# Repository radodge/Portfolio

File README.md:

# Engineering Project Portfolio

Welcome to my collection of hardware and software projects developed through coursework and personal experimentation. This repository gathers small demos and complete applications spanning digital logic design, embedded C programming, PCB layout, ASIC development, and Python-based computer vision image processing.

## Project Index
> Use the categories below to jump directly to work that matches the relevant skills you're interested in.
### Computer Vision Image Processing & Automation
- [Photo Digitization Application - v0](https://github.com/radodge/photo-digitization-v0) – Legacy implementation of my photo 'digitization' Python application.

### Embedded Systems Design
- [CPRE 288 Final Project](CPRE%20288%20Final%20Project/) – Embedded C code for robot movement, sensor processing, and driver abstractions.

### Digital VLSI
- [32-bit CPU Components](32-bit%20CPU%20Components/) – VHDL building blocks for a 32-bit MIPS CPU.
- [Moving Average and Std Dev ASIC](Moving%20Average%20and%20Std%20Dev%20ASIC/) – Custom Verilog ASIC implementing real time computation of moving average and standard deviation.

### PCB Design
- [KiCad Projects](KiCad%20Projects/) – Schematics and board layouts such as an adjustable power supply and a reprogrammable Game Boy Advance cartridge.

## Contact
Questions or collaboration inquiries? Reach out via email at dodger1846@icloud.com or connect on [LinkedIn](https://www.linkedin.com/in/reece-dodge).

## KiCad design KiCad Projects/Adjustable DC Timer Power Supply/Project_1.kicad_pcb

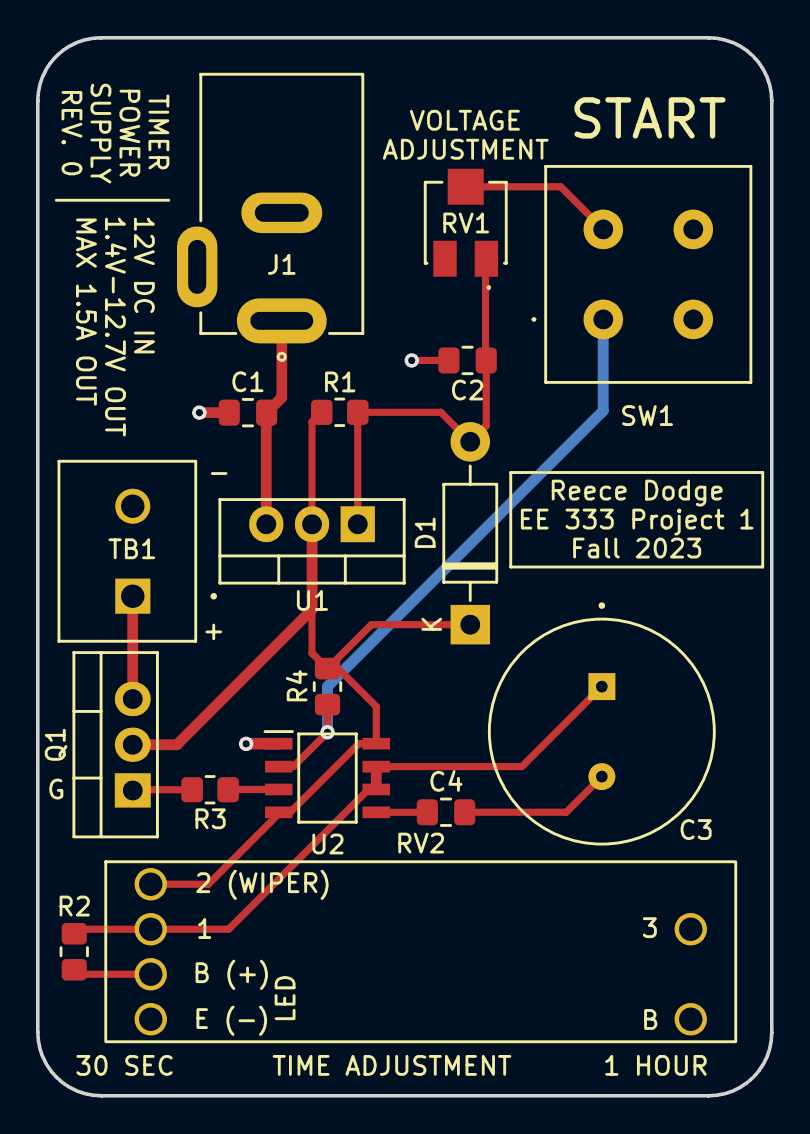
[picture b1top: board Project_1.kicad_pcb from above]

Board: 2 copper layers, 40.8 x 58.8 mm, 17 parts (0 on the bottom side), 11 nets.

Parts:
C1, C2: 10uF; C_0805_2012Metric_Pad1.18x1.45mm_HandSolder
C3: 3300uF; ECA-1CHG332
C4: 0.1uF; C_0805_2012Metric_Pad1.18x1.45mm_HandSolder
D1: 1N4002; D_DO-41_SOD81_P10.16mm_Horizontal
J1: PJ-002A
Q1: Q_NMOS_GDS; TO-220-3_Vertical
R1: 240; R_0805_2012Metric_Pad1.20x1.40mm_HandSolder
R2, R3, R4: 10K; R_0805_2012Metric_Pad1.20x1.40mm_HandSolder
RV1: 2.2K; TRIM_3314J-1-222E
RV2: PTL20-10O0-105B2
SW1: START; D6C90F2LFS
TB1: TB002-500-02BE; CUI_TB002-500-02BE
U1: LM317_SOT-223; TO-220-3_Vertical
U2: NE555D; SOIC127P600X175-8N

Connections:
/V_out: D1.1 (K), Q1.2 (D), R1.1, R4.2, RV2.2 (WIPER), U1.2 (VO), U2.4 (R), U2.8 (VCC)
GND: C1.1, C2.2, C3.N, C4.2, J1.2, RV1.2, RV2.E, SW1.3 (NO_1), TB1.2, U2.1 (GND)
unnamed: C2.1, D1.2 (A), R1.2, RV1.1, U1.1 (ADJ)
unnamed: Q1.1 (G), R3.2
unnamed: Q1.3 (S), TB1.1
unnamed: R2.2, RV2.L
unnamed: C3.P, R2.1, RV2.1 (CCW), U2.6 (THR), U2.7 (DIS)
unnamed: R4.1, SW1.1 (COM_1), U2.2 (TR)
unnamed: C1.2, J1.1, U1.3 (VI)
unnamed: C4.1, U2.5 (CV)
unnamed: R3.1, U2.3 (Q)

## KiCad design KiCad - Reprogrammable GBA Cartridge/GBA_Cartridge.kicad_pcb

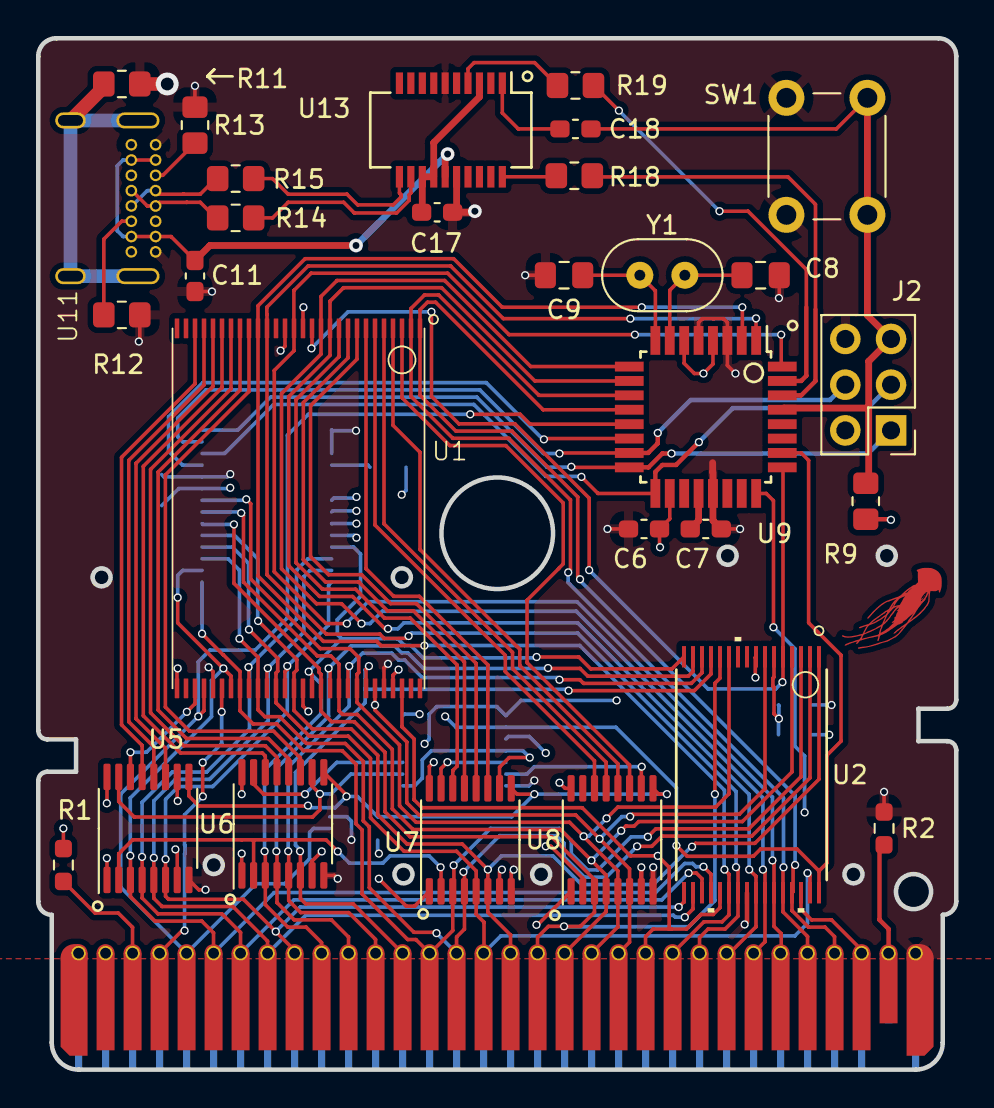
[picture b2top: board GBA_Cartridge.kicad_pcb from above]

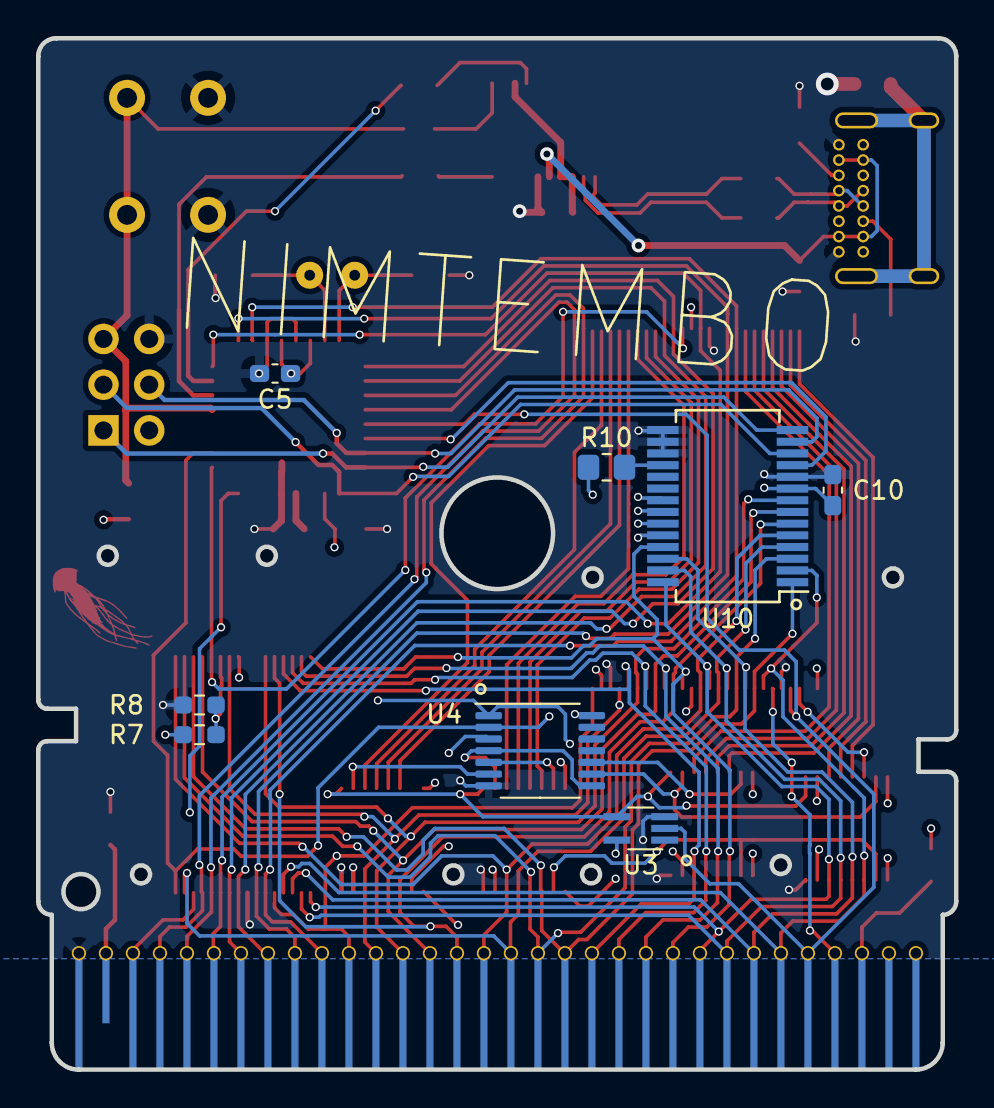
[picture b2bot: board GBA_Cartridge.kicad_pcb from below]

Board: 4 copper layers, 51.0 x 57.3 mm, 39 parts (8 on the bottom side), 78 nets.

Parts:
C5, C6, C7, C10, C17, C18: 0.1uF; C_0603_1608Metric_Pad1.08x0.95mm_HandSolder
C8, C9: 22pF; C_0805_2012Metric_Pad1.18x1.45mm_HandSolder
C11: 10nF; C_0603_1608Metric_Pad1.08x0.95mm_HandSolder
COS1: important
J1: Conn_01x32; GAYBUS
J2: Conn_02x03_Odd_Even; PinHeader_2x03_P2.54mm_Vertical
R1, R2, R7, R8: DNU; R_0603_1608Metric_Pad0.98x0.95mm_HandSolder
R9, R18, R19: 1k; R_0805_2012Metric_Pad1.20x1.40mm_HandSolder
R10: 10k; R_0805_2012Metric_Pad1.20x1.40mm_HandSolder
R11: 1M; R_0805_2012Metric_Pad1.20x1.40mm_HandSolder
R12, R13: 5.11k; R_0805_2012Metric_Pad1.20x1.40mm_HandSolder
R14, R15: 27R; R_0805_2012Metric_Pad1.20x1.40mm_HandSolder
SW1: SW_Push; SW_PUSH_6mm
U1: MT28EW256ABA1LJS-0SIT; 56-TFSOP (18.40mm Width)
U2: FM28V100-TG; TSOP-32
U3: 74AHC1G14SE-7; SOT-353_SC-70-5_Handsoldering
U4: 74LS08; TSSOP-14_4.4x5mm_P0.65mm
U5, U6, U7, U8: SN74LV163APWR; TSSOP-16_4.4x5mm_P0.65mm
U9: TQFP-32_7x7mm_P0.8mm
U10: MCP23S17-E/SS; SSOP-28_5.3x10.2mm_P0.65mm
U11: USB4085-GF-A; USB-C
U13: FT231XS-R; SSOP-20_3.9x8.7mm_P0.635mm
Y1: 16 MHz; xtal

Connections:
+3V3: C5.1, C6.2, C10.1, J1.1, R1.2, R7.2, R9.1, R10.1, U1.14 (RST#), U1.29 (VCCQ), U1.43 (VCC), U1.53 (BYTE#), U2.8 (VDD), U3.5, U4.14 (VCC), U5.1 (~CLR), U5.7 (ENP), U5.10 (ENT), U5.16 (VCC), U6.1 (~CLR), U6.7 (ENP), U6.16 (VCC), U7.1 (~CLR), U7.7 (ENP), U7.16 (VCC), U8.1 (~CLR), U8.7 (ENP), U8.16 (VCC), U9.4 (VCC), U9.6 (VCC), U9.18 (AVCC), U10.9 (VDD)
/Atmega/CS_IOexp: U9.14 (PB2(~SS/OC1B)), U10.11 (~CS)
/Atmega/MISO: J2.1, U9.16 (PB4(MISO)), U10.14 (SO)
/Atmega/MOSI: J2.4, U9.15 (PB3(MOSI/OC2)), U10.13 (SI)
/Atmega/RXD: R18.2, U9.30 (PD0(RXD))
/Atmega/SCK: J2.3, U9.17 (PB5(SCK)), U10.12 (SCK)
/Atmega/TXD: R19.2, U9.31 (PD1(TXD))
/Atmega/~RESET: C18.2, J2.5, R9.2, SW1.1, U9.29 (PC6(~RESET))
/A//D_B0: J1.22, U1.54 (A16), U2.21 (DQ0), U9.24 (PC1(ADC1))
/A//D_B1: J1.23, U1.19 (A17), U2.22 (DQ1), U9.2 (PD4(XCK/T0))
/A//D_B2: J1.24, U1.18 (A18), U2.23 (DQ2), U9.1 (PD3(INT1))
/A//D_B3: J1.25, U1.11 (A19), U2.25 (DQ3), U9.10 (PD6(AIN0))
/A//D_B4: J1.26, U1.12 (A20), U2.26 (DQ4), U9.9 (PD5(T1))
/A//D_B5: J1.27, U1.15 (A21), U2.27 (DQ5), U9.32 (PD2(INT0))
/A//D_B6: J1.28, U1.2 (A22), U2.28 (DQ6), U9.11 (PD7(AIN1))
/A//D_B7: J1.29, U1.1 (A23/RFU), U2.29 (DQ7), U9.12 (PB0(ICP1))
/Counters/A_Latch_B0: U1.31 (A0), U5.14 (QA)
/Counters/A_Latch_B1: U1.26 (A1), U5.13 (QB)
/Counters/A_Latch_B2: U1.25 (A2), U5.12 (QC)
/Counters/A_Latch_B3: U1.24 (A3), U5.11 (QD)
/Counters/A_Latch_B4: U1.23 (A4), U6.14 (QA)
/Counters/A_Latch_B5: U1.22 (A5), U6.13 (QB)
/Counters/A_Latch_B6: U1.21 (A6), U6.12 (QC)
/Counters/A_Latch_B7: U1.20 (A7), U6.11 (QD)
/Counters/A_Latch_B8: U1.10 (A8), U7.14 (QA)
/Counters/A_Latch_B9: U1.9 (A9), U7.13 (QB)
/Counters/A_Latch_B10: U1.8 (A10), U7.12 (QC)
/Counters/A_Latch_B11: U1.7 (A11), U7.11 (QD)
/Counters/A_Latch_B12: U1.6 (A12), U8.14 (QA)
/Counters/A_Latch_B13: U1.5 (A13), U8.13 (QB)
/Counters/A_Latch_B14: U1.4 (A14), U8.12 (QC)
/Counters/A_Latch_B15: U1.3 (A15), U8.11 (QD)
/USB-C/D+: R15.2, U13.11 (USBDP)
/USB-C/D-: R14.2, U13.12 (USBDM)
/USB-C/D_pre+: R15.1, U11.A6 (D+), U11.B6 (D+)
/USB-C/D_pre-: R14.1, U11.A7 (D-), U11.B7 (D-)
/USB-C/V_USB: C11.1, U11.A4 (VBUS), U11.A9 (VBUS), U11.B4 (VBUS), U11.B9 (VBUS), U13.15 (VCC)
/muxA;D//A_B0: J1.6, U1.35 (DQ0), U2.20 (A0), U5.3 (A), U10.2 (GPB1)
/muxA;D//A_B1: J1.7, U1.37 (DQ1), U2.19 (A1), U5.4 (B), U10.26 (GPA5)
/muxA;D//A_B2: J1.8, U1.39 (DQ2), U2.18 (A2), U5.5 (C), U10.27 (GPA6)
/muxA;D//A_B3: J1.9, U1.41 (DQ3), U2.17 (A3), U5.6 (D), U10.28 (GPA7)
/muxA;D//A_B4: J1.10, U1.44 (DQ4), U2.16 (A4), U6.3 (A), U10.25 (GPA4)
/muxA;D//A_B5: J1.11, U1.46 (DQ5), U2.15 (A5), U6.4 (B), U10.24 (GPA3)
/muxA;D//A_B6: J1.12, U1.48 (DQ6), U2.14 (A6), U6.5 (C), U10.23 (GPA2)
/muxA;D//A_B7: J1.13, U1.50 (DQ7), U2.13 (A7), U6.6 (D), U10.22 (GPA1)
/muxA;D//A_B8: J1.14, U1.36 (DQ8), U2.3 (A8), U7.3 (A), U10.1 (GPB0)
/muxA;D//A_B9: J1.15, U1.38 (DQ9), U2.2 (A9), U7.4 (B), U10.3 (GPB2)
/muxA;D//A_B10: J1.16, U1.40 (DQ10), U2.31 (A10), U7.5 (C), U10.4 (GPB3)
/muxA;D//A_B11: J1.17, U1.42 (DQ11), U2.1 (A11), U7.6 (D), U10.5 (GPB4)
/muxA;D//A_B12: J1.18, U1.45 (DQ12), U2.12 (A12), U8.3 (A), U10.6 (GPB5)
/muxA;D//A_B13: J1.19, U1.47 (DQ13), U2.4 (A13), U8.4 (B), U10.7 (GPB6)
/muxA;D//A_B14: J1.20, U1.49 (DQ14), U2.11 (A14), U8.5 (C), U10.8 (GPB7)
/muxA;D//A_B15: J1.21, U1.51 (DA15/A-1), U2.7 (A15), U8.6 (D), U10.21 (GPA0)
/~Chip_Sel2: J1.30, U2.30 (*CE1)
/~Chip_Sel: J1.5, U1.32 (CE#), U3.2, U9.13 (PB1(OC1A))
/~Read: J1.4, U1.34 (OE#), U2.32 (*OE), U4.2, U9.26 (PC3(ADC3))
/~Write: J1.3, R1.1, U1.13 (WE#), U2.5 (*WE), U4.1, U9.25 (PC2(ADC2))
GND: C5.2, C6.1, C7.1, C8.2, C9.2, C10.2, C11.2, C17.2, J1.32, J2.6, R2.2, R8.2, R11.1, R12.1, R13.1, SW1.2, U1.16 (Vpp/WP#), U1.33 (VSS), U1.52 (VSS), U2.24 (GND), U3.3, U4.7 (GND), U5.8 (GND), U6.8 (GND), U7.8 (GND), U8.8 (GND), U9.3 (GND), U9.5 (GND), U9.21 (GND), U10.10 (VSS), U10.15 (A0), U10.16 (A1), U10.17 (A2), U11.A1 (GND), U11.A12 (GND), U11.B1 (GND), U11.B12 (GND), U13.6 (GND), U13.16 (GND)
unnamed: J1.31, R2.1
unnamed: R7.1, R8.1, U2.6 (CE2)
unnamed: U4.3, U5.2 (CLK), U6.2 (CLK), U7.2 (CLK), U8.2 (CLK)
unnamed: U4.9, U5.15 (RCO), U6.10 (ENT)
unnamed: U3.4, U5.9 (~LOAD), U6.9 (~LOAD), U7.9 (~LOAD), U8.9 (~LOAD)
unnamed: U4.10, U6.15 (RCO)
unnamed: U4.4, U4.8, U7.10 (ENT)
unnamed: U4.5, U7.15 (RCO)
unnamed: U4.6, U8.10 (ENT)
unnamed: C7.2, U9.20 (AREF)
unnamed: C8.1, U9.7 (PB6(XTAL1/TOSC1)), Y1.2
unnamed: C9.1, U9.8 (PB7(XTAL2/TOSC2)), Y1.1
unnamed: R10.2, U10.18 (~RESET)
unnamed: R13.2, U11.A5 (CC1)
unnamed: R12.2, U11.B5 (CC2)
unnamed: R11.2, U11.S1 (SHIELD)
unnamed: C17.1, U13.3 (VCCIO), U13.13 (3V3OUT), U13.14 (~RESET)
unnamed: R19.1, U13.4 (RXD)
unnamed: R18.1, U13.20 (TXD)
unnamed: C18.1, U13.1 (~DTR)

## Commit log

2023-10-25 Deleted unused legacy files
2024-04-19 Addition of GBA cart KiCad project
2024-04-19 Reorganized 288 final project file structure
2024-04-19 Added EE 333 project 1
2024-04-19 Renamed folders
2024-07-30 Added CPRE/EE final project
2025-08-21 Added legacy photo digitization application and empty README
2025-08-23 Added README.md for each project. Setting up legacy photo digitization app for easy demos.
2025-08-25 CUDA debugging
2025-08-25 Move legacy v0 to standalone repo
2025-08-25 Add legacy v0 as submodule
2025-08-25 Changes to submodule
2025-08-26 More changes to submodule
2025-08-27 Fix link to Photo Digitization Application - v0
    Updated link for the Photo Digitization Application - v0.
2025-08-27 Reordered project index
2025-08-27 Refactor project links in README.md
